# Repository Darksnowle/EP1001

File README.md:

## Welcome to GitHub Pages

You can use the [editor on GitHub](https://github.com/Darksnowle/EP1001/edit/main/README.md) to maintain and preview the content for your website in Markdown files.

Whenever you commit to this repository, GitHub Pages will run [Jekyll](https://jekyllrb.com/) to rebuild the pages in your site, from the content in your Markdown files.

### Markdown

Markdown is a lightweight and easy-to-use syntax for styling your writing. It includes conventions for

```markdown
Syntax highlighted code block

# Header 1
## Header 2
### Header 3

- Bulleted
- List

1. Numbered
2. List

**Bold** and _Italic_ and `Code` text

[Link](url) and 
```

For more details see [GitHub Flavored Markdown](https://guides.github.com/features/mastering-markdown/).

### Jekyll Themes

Your Pages site will use the layout and styles from the Jekyll theme you have selected in your [repository settings](https://github.com/Darksnowle/EP1001/settings). The name of this theme is saved in the Jekyll `_config.yml` configuration file.

### Support or Contact

Having trouble with Pages? Check out our [documentation](https://docs.github.com/categories/github-pages-basics/) or [contact support](https://github.com/contact) and we’ll help you sort it out.

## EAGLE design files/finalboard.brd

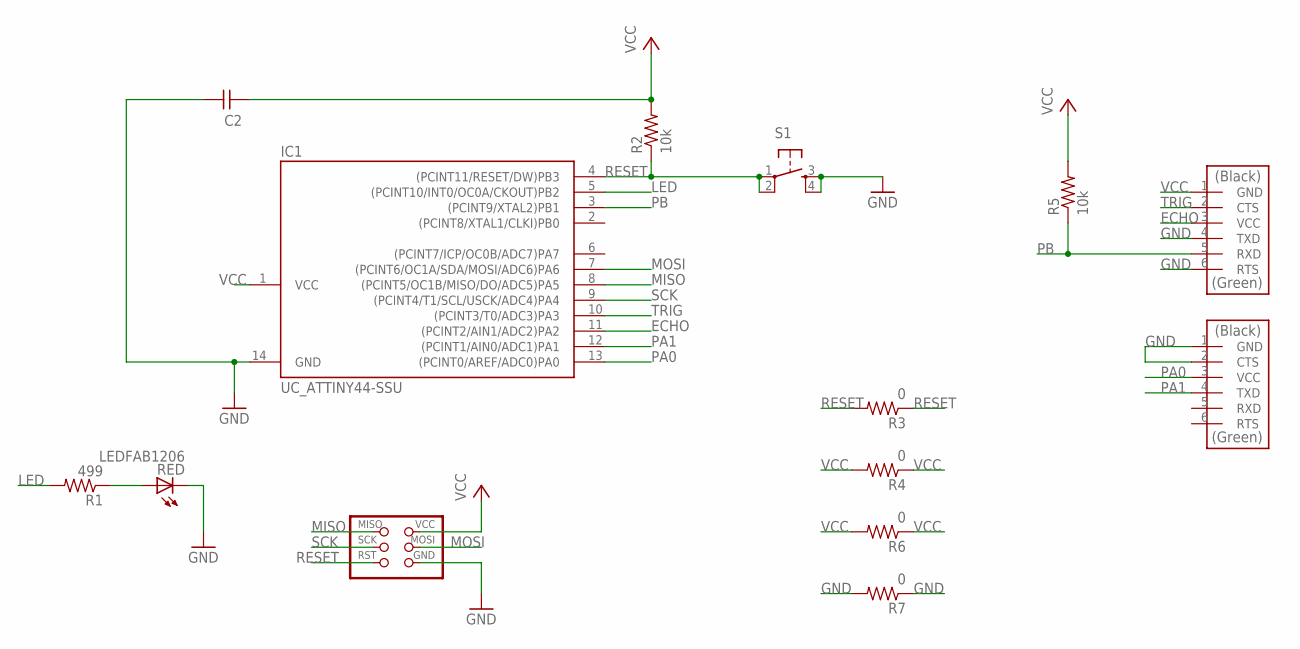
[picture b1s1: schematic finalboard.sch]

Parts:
C2: 1u; C1206FAB
IC1: UC_ATTINY44-SSU; SOIC14
MOTOR: CONN_06_FTDI-SMD-HEADER; 1X06SMD
R1: 499; R1206FAB
R2, R5: 10k; R1206FAB
R3, R4, R6, R7: 0; R1206FAB
RED: LEDFAB1206; LED1206FAB
S1: SW_SWITCH_TACTILE_6MM6MM_SWITCH; 6MM_SWITCH
U$3: CONN_03X2_AVRISPSMD; 2X03SMD
ULTRANPB: CONN_06_FTDI-SMD-HEADER; 1X06SMD

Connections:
ECHO: IC1.11 ((PCINT2/AIN1/ADC2)PA2), ULTRANPB.3 (VCC)
GND: C2.2, IC1.14 (GND), MOTOR.1 (GND), MOTOR.2 (CTS), R7.1, R7.2, RED.2 (C), S1.3 (S), S1.4 (S1), U$3.6 (GND), ULTRANPB.4 (TXD), ULTRANPB.6 (RTS)
LED: IC1.5 ((PCINT10/INT0/OC0A/CKOUT)PB2), R1.2
MISO: IC1.8 ((PCINT5/OC1B/MISO/DO/ADC5)PA5), U$3.1 (MISO)
MOSI: IC1.7 ((PCINT6/OC1A/SDA/MOSI/ADC6)PA6), U$3.4 (MOSI)
unnamed: R1.1, RED.1 (A)
PA0: IC1.13 ((PCINT0/AREF/ADC0)PA0), MOTOR.3 (VCC)
PA1: IC1.12 ((PCINT1/AIN0/ADC1)PA1), MOTOR.4 (TXD)
PB: IC1.3 ((PCINT9/XTAL2)PB1), R5.1, ULTRANPB.5 (RXD)
RESET: IC1.4 ((PCINT11/RESET/DW)PB3), R2.1, R3.1, R3.2, S1.1, S1.2 (P1), U$3.5 (RST)
SCK: IC1.9 ((PCINT4/T1/SCL/USCK/ADC4)PA4), U$3.3 (SCK)
TRIG: IC1.10 ((PCINT3/T0/ADC3)PA3), ULTRANPB.2 (CTS)
VCC: C2.1, IC1.1 (VCC), R2.2, R4.1, R4.2, R5.2, R6.1, R6.2, U$3.2 (VCC), ULTRANPB.1 (GND)

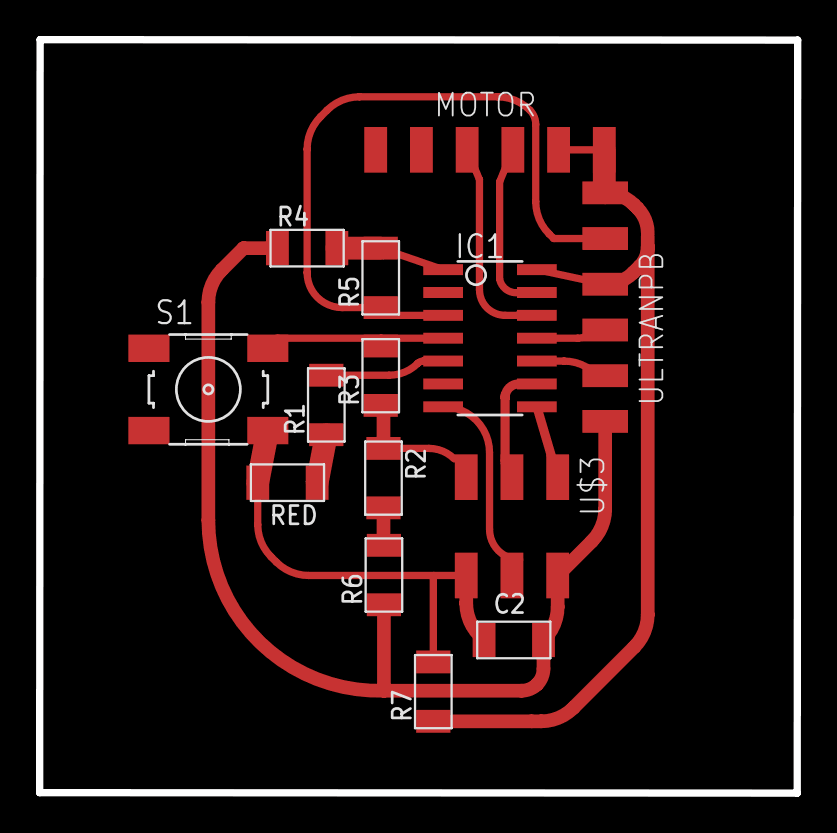
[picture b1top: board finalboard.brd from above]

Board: 2 copper layers, 42.1 x 41.9 mm, 14 parts (0 on the bottom side), 13 nets.

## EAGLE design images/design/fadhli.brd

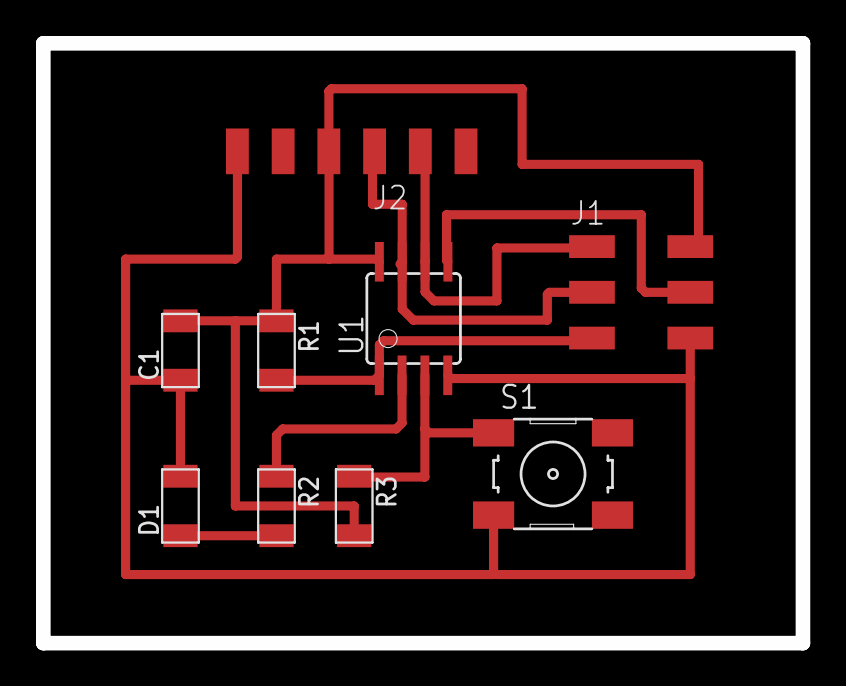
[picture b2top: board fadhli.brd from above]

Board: 2 copper layers, 42.2 x 33.3 mm, 9 parts (0 on the bottom side), 9 nets.

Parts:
C1: 1u; C1206FAB
D1: RED; LED1206FAB
J1: CONN_03X2_AVRISPSMD; 2X03SMD
J2: FTDI; 1X06SMD
R1, R3: 10K; R1206FAB
R2: 499; R1206FAB
S1: switch; 6MM_SWITCH
U1: UC_ATTINY45SI; SOIC8

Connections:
GND: C1.1, D1.2, J1.6, J2.1, S1.3, U1.4
LED: R2.1, U1.2
MISO: J1.1, J2.5, U1.6
MOSI: J1.4, U1.5
unnamed: D1.1, R2.2
PB: R3.1, S1.1, U1.3
RESET: J1.5, R1.2, U1.1
SCK: J1.3, J2.4, U1.7
VCC: C1.2, J1.2, J2.3, R1.1, R3.2, U1.8

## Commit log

2020-10-26 Set theme jekyll-theme-merlot
2021-01-28 programmer update
2021-02-14 molding and casting done
2021-02-26 images
2021-02-26 vcarve
2021-02-26 done
2021-02-26 deleted
